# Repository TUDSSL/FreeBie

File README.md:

# Battery-free Bluetooth That Works

## Abstract
We present an architecture for intermittently-powered wireless communication systems that does not require any changes to the official protocol specification. Our core idea is to save the intermediate state of the wireless protocol to non-volatile memory within each connection interval. The protocol state is then deterministically restored at a predefined (harvested energy-dependent) time, which follows the connection interval. As a case study for our architecture, we introduce FreeBie: a battery-free intermittently-powered Bluetooth Low Energy (BLE) mote. To the best of our knowledge FreeBie is the first battery-free active wireless system that sustains bi-directional communication on intermittent harvested energy. The strength of our architecture is articulated by FreeBie consuming at least 9.5 times less power during device inactivity periods than a state-of-the-art BLE device.

<!--  -->
<!--  -->

## Artifact
We describe the process to reproduce the results presented in the paper.

### Repository structure
The diagram below describes structure and purpose of the most important directories of the FreeBie project.
* * *
 * Hardware
   * design: KiCad design files
   * schematic: PDF schematic
   * manufacturing: Bill of materials, Gerber files (per version)
 * Software
   * bin: Location of compiled application binaries
   * build: Location of build files
   * ckpt-app: Application process files per application
     * fw-update
     * smartwatch
     * template
   * ckpt-os: OS process files
   * config: CMake and project configuration files
   * libs: Drivers for external system components
   * platforms: Pin definitions
   * third-party
     * Cordio: Network process files
 * Evaluation
   * hosts
     * fw-update: Firmware for the firmware update host
     * smartwatch: Android app for smartwatch host
     * end-device
       * softdevice: Power comparison application
   * Plotting
     * plot.sh: Script generating all the plots in the paper
     * *.py: Figure-specific Python script invoked by plot.sh
 * Measurements
     * raw: Raw measurements
     * converted: Measurements converted to CSV format
     * traces: 24H trace and replay script
* * *

### Evaluation Setup
#### Code Generation and Programming Tools.

To compile FreeBie runtime we used the [GNU Arm Embedded Toolchain (9.3.1)](https://developer.arm.com/tools-and-software/open-source-software/developer-tools/gnu-toolchain/gnu-rm/downloads) and [CMake (3.19.1)](https://cmake.org) to build the project. To program the MCU we used the [J-Link debug probe](https://www.segger.com/products/debug-probes/j-link/models/j-link-edu) with the accompanying J-Link software. We used Linux in order compile and evaluate FreeBie. In this artifact, only Linux instructions are provided, although (untested) Windows or Mac OS could also be used to build the system.

#### Trace Recording Tools.

We used [Saleae Logic Pro 16 logic analyzer](http://downloads.saleae.com/specs/Logic+Pro+16+Product+Fact+Sheet.pdf), to record on-device FreeBie signals. To capture and analyze over-the-air master/end-device BLE packets exchanges we used [Nordic Semiconductors nRF sniffer](https://www.nordicsemi.com/Products/Development-tools/nRF-Sniffer-for-Bluetooth-LE) and [Wireshark](https://www.wireshark.org}) as protocol analyzer.

#### Controlled Test Environment.

We put FreeBie at the bottom of a closed light box. A wirelessly-controlled [LED bulb](https://www.philips-hue.com/en-gb/p/hue-white-ambiance-1-pack-e27/8718699673147) was installed at the top of the box to create repeatable and controlled light source. A [luminosity meter](https://www.uni-trend.com/html/product/Environmental/Environmental_Tester/Mini/UT383.html) was placed next to FreeBie mote to measure the exact luminosity projecting onto FreeBie's solar panels.

#### Power Measurement Process.

Connection event as well as the sleep power consumption for the [Packetcraft BLE network stack](https://github.com/packetcraft-inc/stacks), Nordic Semiconductors BLE SoftDevice and our intermittently-powered BLE stack were measured using a [STMicroelectronics X-NUCLEO-LPM01A power measurement board](https://www.st.com/en/evaluation-tools/x-nucleo-lpm01a.html). FreeBie's power consumption whilst the processor domain is off was measured with [Keithley 2450 SMU](https://download.tek.com/datasheet/1KW-60904-2_2450_Datasheet_072021.pdf). Power consumption during sleep and power off was measured at 1.8V. Power consumption of Packetcraft and SoftDevice is measured on the NRF52840 development kit, FreeBie power measurements are measured on the FreeBie mote. The BLE connection event power consumption for Packetcraft and SoftDevice was measured at a 1.8V, while BLE connection event for FreeBie was measured at 2.67V. We measure the connection event after the device has been running for five minutes, selecting a connection event with an empty PDU. The consumed energy results presented in Figure 12 Consumed Energy are computed as the sum of the energy consumed during the selected connection event and during the idle period (power off for FreeBie and sleep for Packetcraft and SoftDevice.).

#### FreeBie Hardware.

In order to reproduce the results of the paper a FreeBie mote is required. In the *Hardware* folder of the repository, all files to reproduce the mote are provided, such as the design files, Gerber files and the bill of materials.

### Building the FreeBie Software

In order to build the FreeBie software, from the *Software/build* directory the following commands need to be executed.

```bash
$ cmake ..
$ make install
```

As a result of these operations, the project is compiled and the resulting programmable binaries of the applications are moved to the *Software/bin* directory. Next, the compiled binary of the application that is being tested should be flashed to the FreeBie mote.

#### Programming the FreeBie Mote.

In order to assist with programming the FreeBie mote during intermittent operation, a button is placed next to the programming header on the mote. When this button is pressed during startup of the MCU, the MCU remains in a perpetual loop, allowing the device to be programmed. Note that this button only works during the start up of the MCU and during operation the mote might be unable to be flashed as the power to the MCU may be switched off.

## Results Reproduction

### Smartwatch Application

In order to reproduce the results related to the smartwatch application please make sure that the smartwatch binary is programmed to the FreeBie mote first.

#### Building the Android Application.

In order to build the Android application, open the project (located in *evaluation/hosts/smartwatch*) in the Android Studio and then proceed with building the APK. Then a *.apk* file should be available in the *evaluation/hosts/smartwatch/build/outputs/apk* directory of the project. The APK must then be installed on the phone through Android Studio or transferred to the phone and installed manually. When opening the app for the first time, it will ask for permissions that must be granted in order for the app to be able to function. For more information please refer to the [Android Developer website]().

#### Measurement.

First the logic analyzer is connected to the testpoints on the FreeBie mote. These testpoints provide the tracing information about the system state used to generate Figure 11 FreeBie smartwatch operation. For the measurement, the programmed FreeBie mote with the smartwatch binary is placed in the light box. The phone should be placed within range of the FreeBie mote for the devices to be able to connect. Next the variable light should be set to output the amount of light specified in the desired scenario to be replicated.

When the light is switched on the FreeBie mote starts harvesting energy and when enough energy is harvested the FreeBie mote should automatically switch on. The smartphone should then automatically connect to the FreeBie mote and time should appear on the LCD screen.

#### 24 hour experiment.

For the 24 hour experiment the same procedure as before is used, but instead of a static lighting, a script (available in the *Measurements/traces* directory) is used to replay a prerecorded luminosity trace of a person wearing a smartwatch for 24 hours. In order to execute the Python script, first the dependencies have to be installed, assuming Python is already installed. For this the following command needs to be executed.

```bash
$ cd Measurements/traces
$ pip install -r requirements.txt
```

Second the tool communicating with the light has to be installed and configured. Please follow the instructions on the website of the [tool](https://github.com/bahamas10/hue-cli). After the software is able to control the light, the script can be executed, replaying 24H of the prerecorded light trace.

```bash
$ python replay_lux.py -f \
  logger-2021-11-20_09-36-46-549.csv -skips 5
```

### Firmware Update Application

We first note that in order to reproduce the results presented in the smartwatch application please make sure the *fw-update* binary is programmed to the FreeBie mote.

#### Building and Flashing the Host Firmware.

First plug in the development kit and make sure that is is powered and detected. Then from the main project directory execute the following command.

```bash
$ cd Evaluation/hosts/          \
     fw-update/  \
     nRF5_SDK_17.0.2/           \
     examples/ble_central/      \
     ble_app_custom_c/          \
     pca10056/s140/armgcc
$ make
$ make flash_softdevice
$ make flash
```

The development kit should now be flashed with the correct firmware. Turn the development kit off and on. Now it is ready to start the firmware update as soon as the FreeBie mote is detected.

#### Measurement.

In order to generate the Evaluation of firmware update plot in FreeBie Evaluation section, the logic analyzer is connected to the test points on the FreeBie mote. These test points provide the tracing information about the system state used to generate Figure 13 Evaluation of firmware update. For the measurement, the programmed FreeBie mote with the *fw-update* binary is placed in the light box. The development kit, acting as firmware update host, should be placed within range of the FreeBie mote for the devices to be able to connect. For the firmware update application we did not connect the display to the FreeBie mote.

When the light is switched on the FreeBie mote starts harvesting energy and when enough energy is harvested the FreeBie mote should automatically switch on. The firmware update host should connect to the FreeBie mote and the firmware update should start automatically.

### Reference Comparison

In order to produce figures 8, 9 and 12 we used a minimal working example (named *template*) of our software that only actively uses the network process and the OS process. In this application after the BLE connection is established and the database discovery has been completed, only empty packets are sent. Hence, this forms a point of reference for other experiments.

#### Template Configuration.

From within the *CMakefile* file of *template*, checkpointing can be switched off by commenting the following lines:
```CMake
set(CHECKPOINTING 1)
set(CHECKPOINTING_TIMING 1)
```
Without checkpointing enabled this example serves as the Packetcraft comparison point and is representative of traditional operation; with checkpointing enabled---as FreeBie. When the checkpointing is active, a connection update request to the selected parameters is sent after connecting. To force the same behavior for the non-checkpointing version, the line *set(COMPARE_NO_CHECKPOINT 1)* needs to be uncommented. When modifying the CMakefiles, the code has to be recompiled with the same steps as described in Section Building the FreeBie Software.

#### Intermittent versus Non-intermittent.

In order to reproduce the results in Figure 8 the FreeBie mote is again placed in a light box at the specified light level and the information about the system state are recorded by the logic analyzer. The experiment is ran for both checkpointing enabled and checkpointing disabled. The non-checkpointed version runs out of energy and not be able to recover the connection as the system state is lost.

#### Connection Recovery.

For the results in Figure 9, the FreeBie mote is not powered by the solar panels but through an external power supply connected to the test point *VSol* on the back of the FreeBie mote. In this case *template* with connection recovery enabled (*set(RECOVER_CONNECTIONS 1)*) and checkpointing enabled is used. After a connection to the FreeBie mote has been established, the power to the device is disabled until the device suffers from a power failure. Then power is resumed and the device attempts recovery.

#### Power Measurement.

For the results in Figure 12 *template* is used with checkpointing disabled, serving as the Packetcraft comparison point; with checkpointing enabled---as FreeBie. As the comparison point of SoftDevice the code provided in *Evaluation/end-device/softdevice* is used. From the main project directory the code can be compiled and flashed using the following commands.

```bash
$ cd Evaluation/end-device/softdevice/ \
     examples/ble_peripheral/ \
     ble_app_pwr_profiling/ \
     pca10056/s140/armgcc
$ make
$ make flash_softdevice
$ make flash
```

Please refer to the Evaluation Setup Section for more information about the power measurement process.

### Plotting

By executing the *plot.sh* script in the *Plotting* directory all of the plots can be generated. Please note that due to the size of the 24 hour plot this might take more than 15 minutes and requires a system with at least 16GB of RAM. All plotting scripts use Python and assume Python is installed on the system; all Python dependencies can be installed via the *requirements.txt* file using the following commands.

Since the measurements files are large they are only included in the version of the artifact hosted on [Zenodo](https://doi.org/10.5281/zenodo.6583725)

```bash
$ cd Plotting
$ pip install -r requirements.txt
$ plot.sh
```

## License
The Project adopts the MIT license unless noted otherwise, As Packetcraft licenses its software stack under the Apache 2.0 license our code in the folder Software also adopts this license unless noted otherwise.

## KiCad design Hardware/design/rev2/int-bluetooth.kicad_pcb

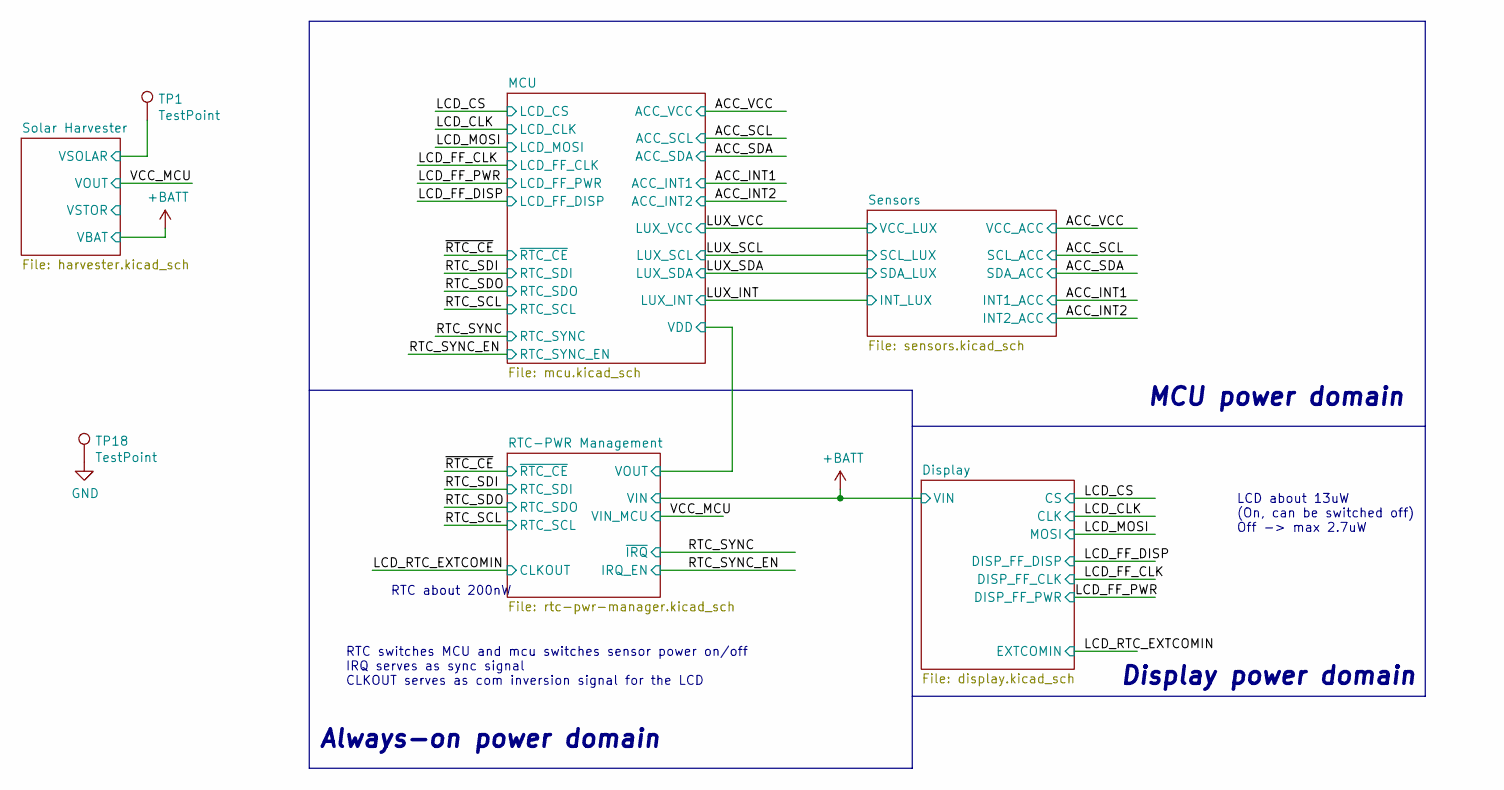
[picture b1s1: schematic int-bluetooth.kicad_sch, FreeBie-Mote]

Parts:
TP1, TP18: TestPoint; SMOX_PCB_TESTPOINT; MPN SMOX/060/B1/HT

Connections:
/Solar Harvester/VSOLAR: TP1.1; also elsewhere on the board
GND: TP18.1; also elsewhere on the board

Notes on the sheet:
Display power domain
LCD about 13uW (On, can be switched off) Off -> max 2.7uW
RTC about 200nW
Always-on power domain
RTC switches MCU and mcu switches sensor power on/off IRQ serves as sync signal CLKOUT serves as com inversion signal for the LCD
MCU power domain

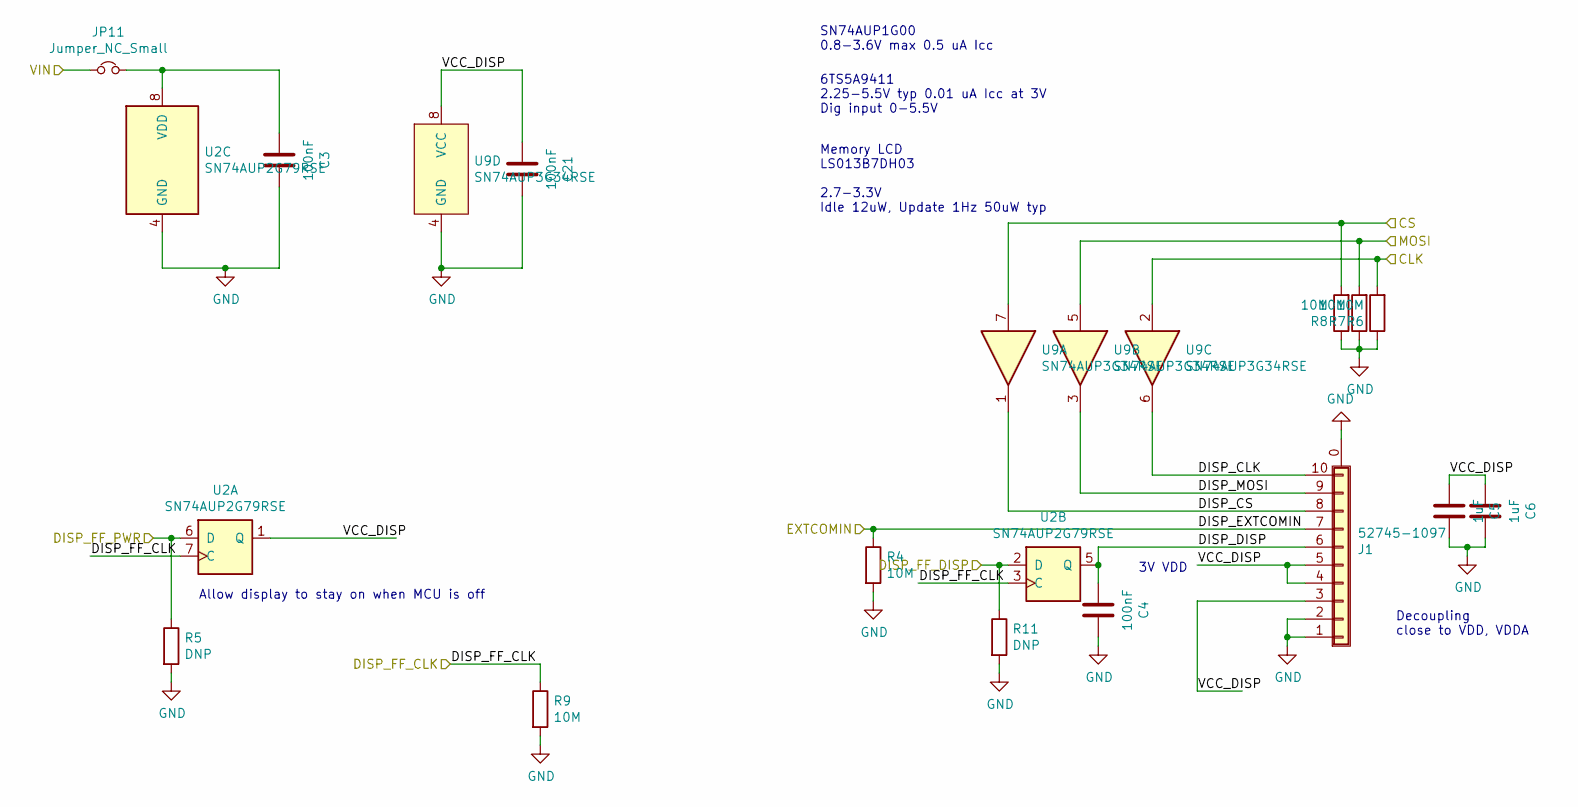
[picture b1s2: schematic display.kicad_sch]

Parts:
C3, C4, C21: 100nF; C_0402_1005Metric; MPN GRM155R71C104KA88J
C5, C6: 1uF; C_0402_1005Metric; MPN 0402ZD105KAT2A
J1: 52745-1097; FPC_10_TOP; MPN 52745-1097
JP11: Jumper_NC_Small; SolderJumper-small-nc
R4, R6, R7, R8, R9: 10M; R_0402_1005Metric; MPN RC0402FR-0710ML
R5, R11: DNP; R_0402_1005Metric
U2: SN74AUP2G79RSE; Texas_RSE_8_UQFN; MPN SN74AUP2G79RSE
U9: SN74AUP3G34RSE; Texas_RSE_8_UQFN; MPN SN74AUP3G34RSE

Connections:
+BATT: JP11.1; also elsewhere on the board
/Display/DISP_CLK: J1.10, U9.6
/Display/DISP_CS: J1.8, U9.1
/Display/DISP_DISP: C4.1, J1.6, U2.5 (Q)
/Display/DISP_MOSI: J1.9, U9.3
/Display/VCC_DISP: C5.1, C6.1, C21.1, J1.3, J1.4, J1.5, U2.1 (Q), U9.8 (VCC)
/LCD_CLK: R6.2, U9.2; also elsewhere on the board
/LCD_CS: R8.2, U9.7; also elsewhere on the board
/LCD_FF_CLK: R9.1, U2.3 (C), U2.7 (C); also elsewhere on the board
/LCD_FF_DISP: R11.1, U2.2 (D); also elsewhere on the board
/LCD_FF_PWR: R5.1, U2.6 (D); also elsewhere on the board
/LCD_MOSI: R7.2, U9.5; also elsewhere on the board
/LCD_RTC_EXTCOMIN: J1.7, R4.1; also elsewhere on the board
GND: C3.2, C4.2, C5.2, C6.2, C21.2, J1.0 (Shield), J1.1, J1.2, R4.2, R5.2, R6.1, R7.1, R8.1, R9.2, R11.2, U2.4 (GND), U9.4 (GND); also elsewhere on the board
unnamed: C3.1, JP11.2, U2.8 (VDD)

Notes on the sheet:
Memory LCD LS013B7DH03 2.7-3.3V Idle 12uW, Update 1Hz 50uW typ
SN74AUP1G00 0.8-3.6V max 0.5 uA Icc
Allow display to stay on when MCU is off
Decoupling close to VDD, VDDA
3V VDD
6TS5A9411 2.25-5.5V typ 0.01 uA Icc at 3V Dig input 0-5.5V

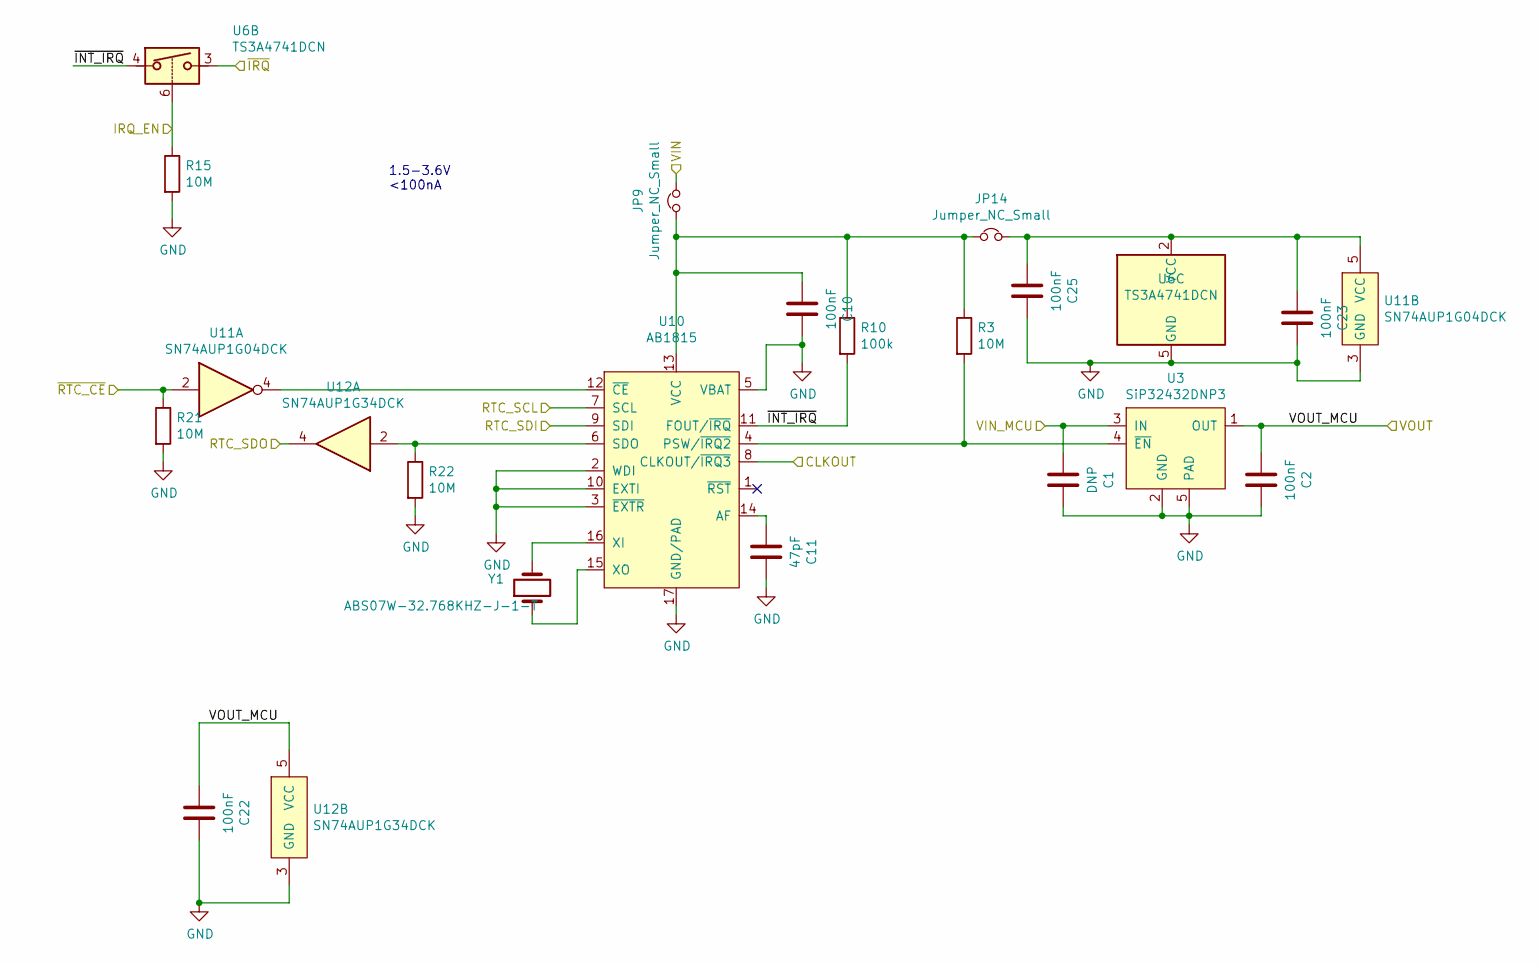
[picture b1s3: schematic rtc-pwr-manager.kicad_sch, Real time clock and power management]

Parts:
C1: DNP; C_0402_1005Metric
C2, C10, C22, C23, C25: 100nF; C_0402_1005Metric; MPN GRM155R71C104KA88J
C11: 47pF; C_0402_1005Metric; MPN GJM1555C1H470FB01D
JP9, JP14: Jumper_NC_Small; SolderJumper-small-nc
R3, R15, R21, R22: 10M; R_0402_1005Metric; MPN RC0402FR-0710ML
R10: 100k; R_0402_1005Metric; MPN RC0402FR-07100KL
U3: SiP32432DNP3; DFN-4-1EP_1.6x1.2mm_P0.5mm_EP; MPN SIP32432DNP3-T1GE4
U6: TS3A4741DCN; SOT-23-8; MPN TS3A4741DCN
U10: AB1815; QFN-16-1EP_3x3mm_P0.5mm_EP1.75x1.75mm_ThermalVias; MPN AM1815
U11: SN74AUP1G04DCK; Texas_R-PDSO-G5; MPN SN74AUP1G04DCK
U12: SN74AUP1G34DCK; Texas_R-PDSO-G5; MPN SN74AUP1G34DCK
Y1: ABS07W-32.768KHZ-J-1-T; Crystal_SMD_3215-2Pin_3.2x1.5mm; MPN ABS07W-32.768KHZ-J-1-T

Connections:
+BATT: JP9.2; also elsewhere on the board
/LCD_RTC_EXTCOMIN: U10.8 (CLKOUT/~IRQ3); also elsewhere on the board
/RTC-PWR Management/VOUT_MCU: C2.1, C22.1, U3.1 (OUT), U12.5 (VCC); also elsewhere on the board
/RTC-PWR Management/~INT_IRQ: R10.2, U6.4, U10.11 (FOUT/~IRQ)
/RTC_SCL: U10.7 (SCL); also elsewhere on the board
/RTC_SDI: U10.9 (SDI); also elsewhere on the board
/RTC_SDO: U12.4; also elsewhere on the board
/RTC_SYNC: U6.3; also elsewhere on the board
/RTC_SYNC_EN: R15.1, U6.6; also elsewhere on the board
/VCC_MCU: C1.1, U3.3 (IN); also elsewhere on the board
/~RTC_CE: R21.1, U11.2; also elsewhere on the board
GND: C1.2, C2.2, C10.2, C11.2, C22.2, C23.2, C25.2, R15.2, R21.2, R22.2, U3.2 (GND), U3.5 (PAD), U6.5 (GND), U10.2 (WDI), U10.3 (~EXTR), U10.5 (VBAT), U10.10 (EXTI), U10.17 (GND/PAD), U11.3 (GND), U12.3 (GND); also elsewhere on the board
unnamed: C10.1, JP9.1, JP14.1, R3.1, R10.1, U10.13 (VCC)
unnamed: C11.1, U10.14 (AF)
unnamed: C23.1, C25.1, JP14.2, U6.2 (VCC), U11.5 (VCC)
unnamed: R3.2, U3.4 (~EN), U10.4 (PSW/~IRQ2)
unnamed: R22.1, U10.6 (SDO), U12.2
unnamed: U10.12 (~CE), U11.4
unnamed: U10.15 (XO), Y1.1
unnamed: U10.16 (XI), Y1.2

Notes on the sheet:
1.5-3.6V <100nA

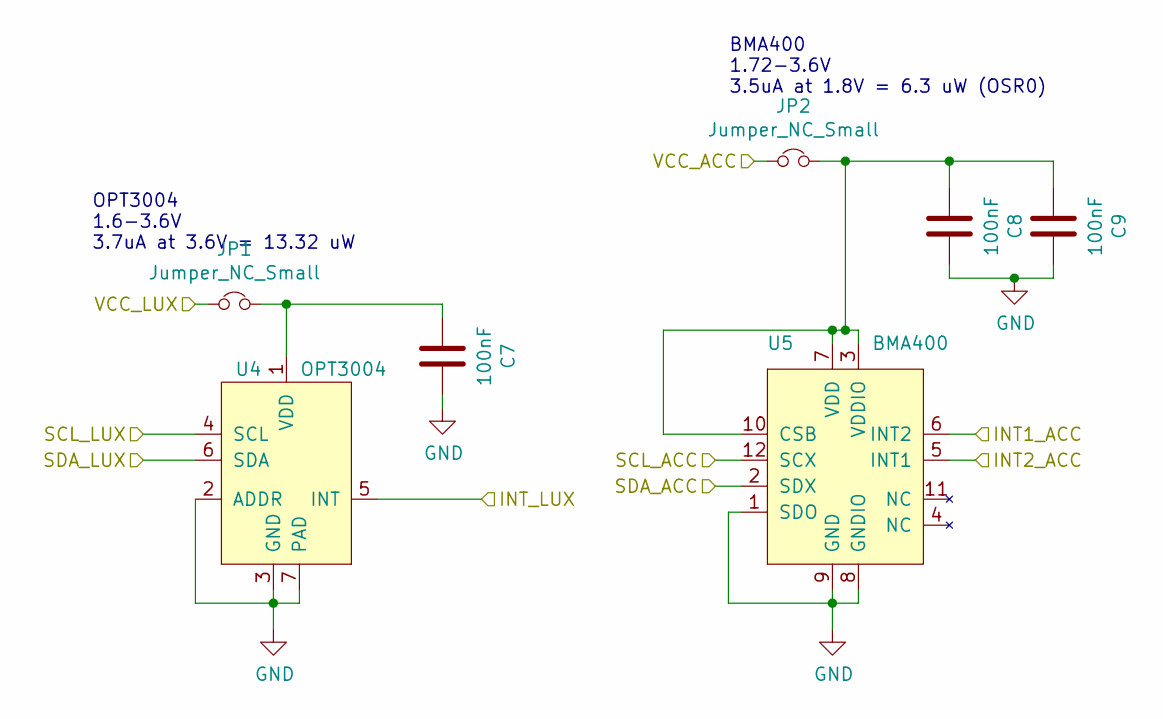
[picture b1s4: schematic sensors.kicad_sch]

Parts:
C7, C8, C9: 100nF; C_0402_1005Metric; MPN GRM155R71C104KA88J
JP1, JP2: Jumper_NC_Small; SolderJumper-small-nc
U4: OPT3004; USON6-OPT3004; MPN OPT3004DNPR
U5: BMA400; MPN BMA400

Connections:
/ACC_INT1: U5.6 (INT2); also elsewhere on the board
/ACC_INT2: U5.5 (INT1); also elsewhere on the board
/ACC_SCL: U5.12 (SCX); also elsewhere on the board
/ACC_SDA: U5.2 (SDX); also elsewhere on the board
/ACC_VCC: JP2.1; also elsewhere on the board
/LUX_INT: U4.5 (INT); also elsewhere on the board
/LUX_SCL: U4.4 (SCL); also elsewhere on the board
/LUX_SDA: U4.6 (SDA); also elsewhere on the board
/LUX_VCC: JP1.1; also elsewhere on the board
GND: C7.2, C8.2, C9.2, U4.2 (ADDR), U4.3 (GND), U4.7 (PAD), U5.1 (SDO), U5.8 (GNDIO), U5.9 (GND); also elsewhere on the board
unnamed: C7.1, JP1.2, U4.1 (VDD)
unnamed: C8.1, C9.1, JP2.2, U5.3 (VDDIO), U5.7 (VDD), U5.10 (CSB)

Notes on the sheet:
OPT3004 1.6-3.6V 3.7uA at 3.6V = 13.32 uW
BMA400 1.72-3.6V 3.5uA at 1.8V = 6.3 uW (OSR0)

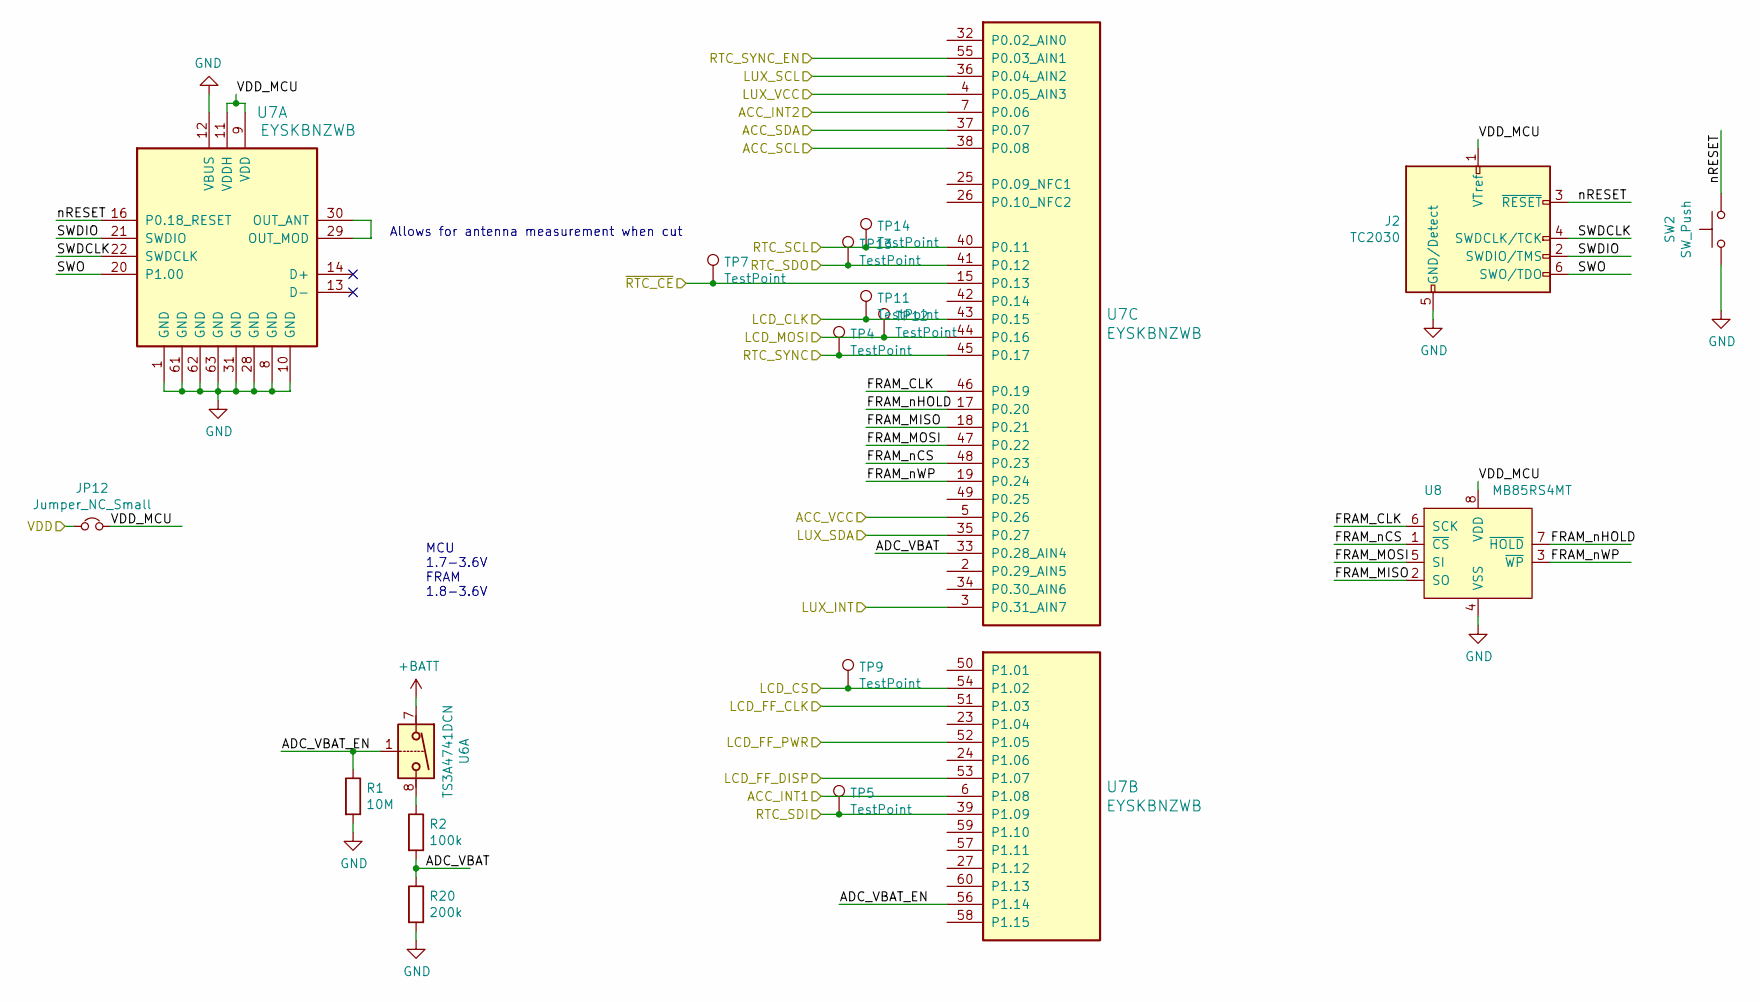
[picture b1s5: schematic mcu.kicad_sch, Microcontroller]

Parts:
J2: TC2030; Tag-Connect_TC2030-IDC-NL_2x03_P1.27mm_Vertical
JP12: Jumper_NC_Small; SolderJumper-small-nc
R1: 10M; R_0402_1005Metric; MPN RC0402FR-0710ML
R2: 100k; R_0402_1005Metric; MPN RC0402FR-07100KL
R20: 200k; R_0402_1005Metric; MPN RC0402FR-07200KL
SW2: SW_Push; SW_SPST_B3U-1000P; MPN B3U-1000P
TP4, TP5, TP7, TP9, TP11, TP12, TP13, TP14: TestPoint; SMOX_PCB_TESTPOINT; MPN SMOX/060/B1/HT
U6: TS3A4741DCN; SOT-23-8; MPN TS3A4741DCN
U7: EYSKBNZWB; MPN EYSKBNZWB
U8: MB85RS4MT; SO-8_5.3x6.2mm_P1.27mm; MPN MB85RS4MT

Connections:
+BATT: U6.7; also elsewhere on the board
/ACC_INT1: U7.6 (P1.08); also elsewhere on the board
/ACC_INT2: U7.7 (P0.06); also elsewhere on the board
/ACC_SCL: U7.38 (P0.08); also elsewhere on the board
/ACC_SDA: U7.37 (P0.07); also elsewhere on the board
/ACC_VCC: U7.5 (P0.26); also elsewhere on the board
/LCD_CLK: TP11.1, U7.43 (P0.15); also elsewhere on the board
/LCD_CS: TP9.1, U7.54 (P1.02); also elsewhere on the board
/LCD_FF_CLK: U7.51 (P1.03); also elsewhere on the board
/LCD_FF_DISP: U7.53 (P1.07); also elsewhere on the board
/LCD_FF_PWR: U7.52 (P1.05); also elsewhere on the board
/LCD_MOSI: TP12.1, U7.44 (P0.16); also elsewhere on the board
/LUX_INT: U7.3 (P0.31_AIN7); also elsewhere on the board
/LUX_SCL: U7.36 (P0.04_AIN2); also elsewhere on the board
/LUX_SDA: U7.35 (P0.27); also elsewhere on the board
/LUX_VCC: U7.4 (P0.05_AIN3); also elsewhere on the board
/MCU/ADC_VBAT: R2.2, R20.1, U7.33 (P0.28_AIN4)
/MCU/ADC_VBAT_EN: R1.1, U6.1, U7.56 (P1.14)
/MCU/FRAM_CLK: U7.46 (P0.19), U8.6 (SCK)
/MCU/FRAM_MISO: U7.18 (P0.21), U8.2 (SO)
/MCU/FRAM_MOSI: U7.47 (P0.22), U8.5 (SI)
/MCU/FRAM_nCS: U7.48 (P0.23), U8.1 (~CS)
/MCU/FRAM_nHOLD: U7.17 (P0.20), U8.7 (~HOLD)
/MCU/FRAM_nWP: U7.19 (P0.24), U8.3 (~WP)
/MCU/SWDCLK: J2.4 (SWDCLK/TCK), U7.22 (SWDCLK)
/MCU/SWDIO: J2.2 (SWDIO/TMS), U7.21 (SWDIO)
/MCU/SWO: J2.6 (SWO/TDO), U7.20 (P1.00)
/MCU/VDD_MCU: J2.1 (VTref), JP12.2, U7.9 (VDD), U7.11 (VDDH), U8.8 (VDD)
/MCU/nRESET: J2.3 (~RESET), SW2.2, U7.16 (P0.18_RESET)
/RTC-PWR Management/VOUT_MCU: JP12.1; also elsewhere on the board
/RTC_SCL: TP14.1, U7.40 (P0.11); also elsewhere on the board
/RTC_SDI: TP5.1, U7.39 (P1.09); also elsewhere on the board
/RTC_SDO: TP13.1, U7.41 (P0.12); also elsewhere on the board
/RTC_SYNC: TP4.1, U7.45 (P0.17); also elsewhere on the board
/RTC_SYNC_EN: U7.55 (P0.03_AIN1); also elsewhere on the board
/~RTC_CE: TP7.1, U7.15 (P0.13); also elsewhere on the board
GND: J2.5 (GND/Detect), R1.2, R20.2, SW2.1, U7.1 (GND), U7.8 (GND), U7.10 (GND), U7.12 (VBUS), U7.28 (GND), U7.31 (GND), U7.61 (GND), U7.62 (GND), U7.63 (GND), U8.4 (VSS); also elsewhere on the board
unnamed: R2.1, U6.8
unnamed: U7.29 (OUT_MOD), U7.30 (OUT_ANT)

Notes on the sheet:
MCU 1.7-3.6V FRAM 1.8-3.6V
Allows for antenna measurement when cut

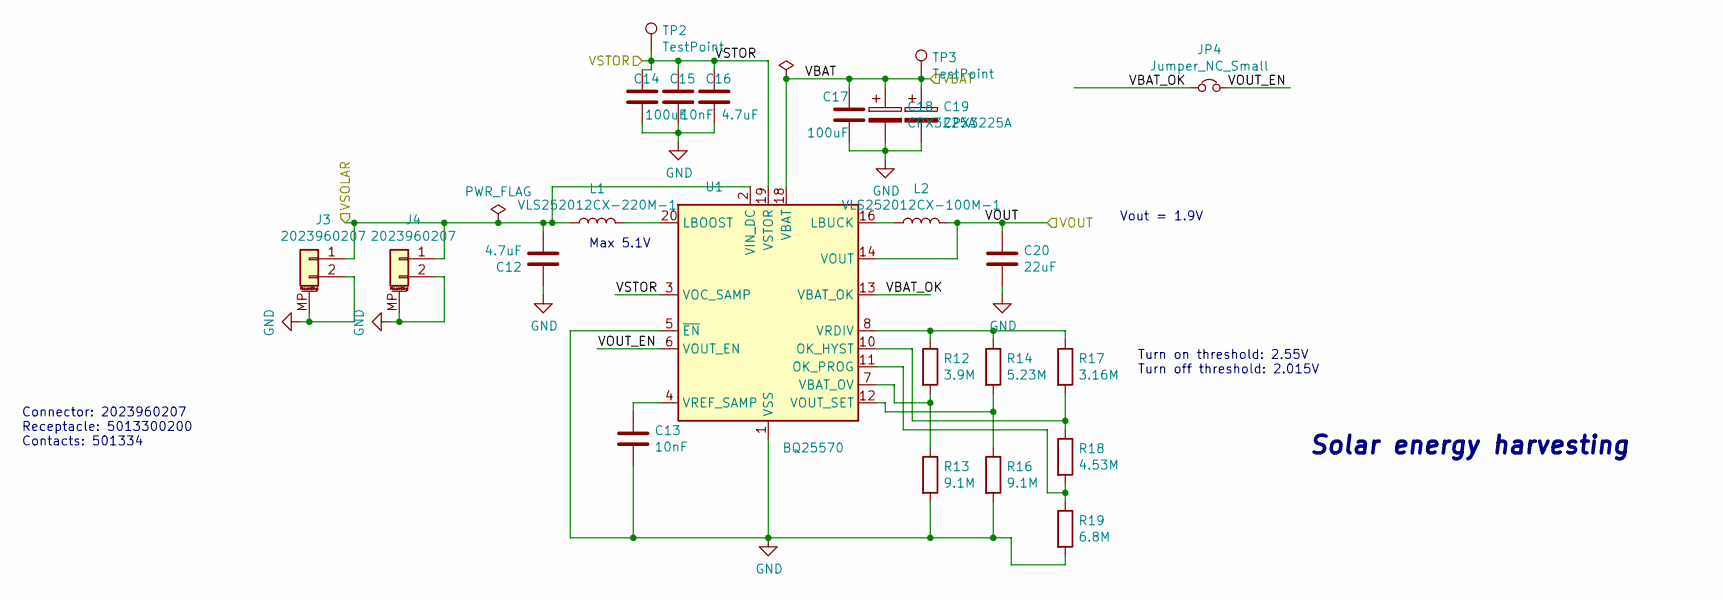
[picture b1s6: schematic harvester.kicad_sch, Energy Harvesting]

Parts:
C12, C16: 4.7uF; C_0402_1005Metric; MPN LMK105BBJ475MVLF
C13, C15: 10nF; C_0402_1005Metric; MPN GCM155R71H103KA55D
C14, C17: 100uF; C_1210_3225Metric
C18, C19: CPX3225A; MPN CPX3225A
C20: 22uF; C_0603_1608Metric; MPN GRM188R60J226MEA0D
J3, J4: 2023960207; Molex_Pico-Clasp_202396-0207_1x02-1MP_P1.00mm_Horizontal; MPN 202396-0207
JP4: Jumper_NC_Small; SolderJumper-small-nc
L1: VLS252012CX-220M-1; VLS252012CX-1; MPN VLS252012CX-220M-1
L2: VLS252012CX-100M-1; VLS252012CX-1; MPN VLS252012CX-100M-1
R12: 3.9M; R_0402_1005Metric; MPN MCHVR02FTFY3904
R13, R16: 9.1M; R_0402_1005Metric; MPN CRCW04029M10FKED
R14: 5.23M; R_0402_1005Metric; MPN CRCW04025M23FKED
R17: 3.16M; R_0402_1005Metric; MPN CRCW04023M16FKED
R18: 4.53M; R_0402_1005Metric; MPN RMCF0402FT4M53
R19: 6.8M; R_0402_1005Metric; MPN MCHVR02FTFY6804
TP2, TP3: TestPoint; SMOX_PCB_TESTPOINT; MPN SMOX/060/B1/HT
U1: BQ25570; QFN-20-1EP_3.5x3.5mm_P0.5mm_EP2x2mm; MPN BQ25570RGR

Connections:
+BATT: C17.2, C18.1, C19.1, TP3.1, U1.18 (VBAT); also elsewhere on the board
/Solar Harvester/VBAT_OK: JP4.1, U1.13 (VBAT_OK)
/Solar Harvester/VOUT_EN: JP4.2, U1.6 (VOUT_EN)
/Solar Harvester/VSOLAR: C12.2, J3.1, J4.1, L1.1, U1.2 (VIN_DC); also elsewhere on the board
/Solar Harvester/VSTOR: C14.2, C15.2, C16.2, TP2.1, U1.3 (VOC_SAMP), U1.19 (VSTOR)
/VCC_MCU: C20.1, L2.2, U1.14 (VOUT); also elsewhere on the board
GND: C12.1, C13.2, C14.1, C15.1, C16.1, C17.1, C18.2, C19.2, C20.2, J3.2, J3.MP (MountPin), J4.2, J4.MP (MountPin), R13.2, R16.2, R19.2, U1.1 (VSS), U1.5 (~EN), U1.9 (VSS), U1.15 (VSS), U1.17 (VSS), U1.21 (VSS); also elsewhere on the board
unnamed: C13.1, U1.4 (VREF_SAMP)
unnamed: L1.2, U1.20 (LBOOST)
unnamed: L2.1, U1.16 (LBUCK)
unnamed: R12.1, R14.1, R17.1, U1.8 (VRDIV)
unnamed: R12.2, R13.1, U1.7 (VBAT_OV)
unnamed: R14.2, R16.1, U1.12 (VOUT_SET)
unnamed: R17.2, R18.1, U1.10 (OK_HYST)
unnamed: R18.2, R19.1, U1.11 (OK_PROG)

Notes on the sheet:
Max 5.1V
Solar energy harvesting
Vout = 1.9V
Turn on threshold: 2.55V Turn off threshold: 2.015V
Connector: 2023960207 Receptacle: 5013300200 Contacts: 501334

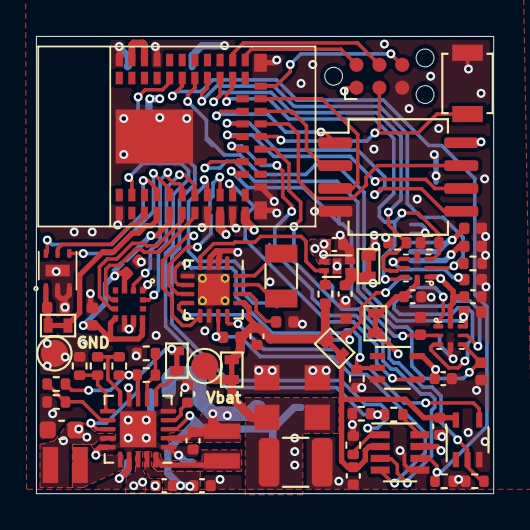
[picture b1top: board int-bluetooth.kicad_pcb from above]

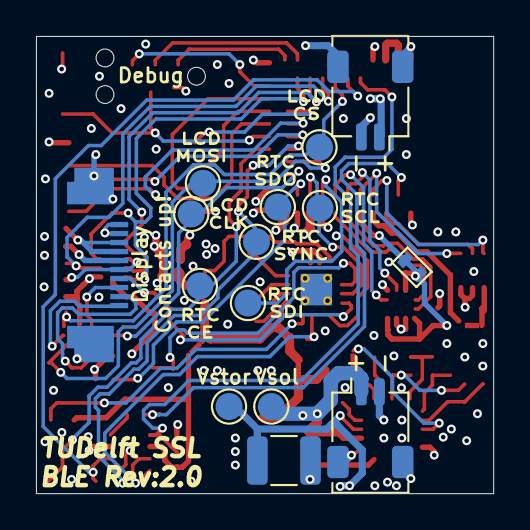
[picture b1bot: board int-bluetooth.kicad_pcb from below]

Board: 4 copper layers, 25.4 x 25.4 mm, 85 parts (15 on the bottom side), 70 nets.

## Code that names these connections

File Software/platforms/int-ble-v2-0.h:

/*************************************************************************************************/
/*!
 *  Copyright (c) 2022 Delft University of Technology.
 *  Jasper de Winkel, Haozhe Tang and Przemyslaw Pawelczak
 *
 *  Licensed under the Apache License, Version 2.0 (the "License");
 *  you may not use this file except in compliance with the License.
 *  You may obtain a copy of the License at
 *
 *      http://www.apache.org/licenses/LICENSE-2.0
 *
 *  Unless required by applicable law or agreed to in writing, software
 *  distributed under the License is distributed on an "AS IS" BASIS,
 *  WITHOUT WARRANTIES OR CONDITIONS OF ANY KIND, either express or implied.
 *  See the License for the specific language governing permissions and
 *  limitations under the License.
 */
/*************************************************************************************************/


#ifndef PLATFORMS_INT_BLE_V2_0_H_
#define PLATFORMS_INT_BLE_V2_0_H_

#include "nrf.h"

// LCD
#define LCD_CLK 15 // P0.15
#define LCD_MOSI 16 // P0.16
#define LCD_CS 34 // P1.02

#define LCD_FF_CLK 35 // P1.03
#define LCD_FF_PWR 37 // P1.05
#define LCD_FF_DISP 39 // P1.07

#ifndef LCD_PINS_OCCUPIED
#define DEBUG_INFO_NET_CKPT LCD_CLK
#define DEBUG_INFO_FW_CONTENT LCD_MOSI
#define DEBUG_INFO_APP_CKPT LCD_CS
#endif

// Lux
#define LUX_VCC 5 // P0.05A
#define LUX_SCL 4 // P0.04A
#define LUX_SDA 27 // P0.27

#define LUX_INT 31 // P0.31A

#define DEBUG_INFO_CKPT LUX_SCL
#define DEBUG_INFO_BLE LUX_SDA
#define DEBUG_INFO_APP LUX_INT

// Acc
#define ACC_VCC 26 // P0.26
#define ACC_SCL 8 // P0.08
#define ACC_SDA 7 // P0.07

#define ACC_INT1 40 // P1.08
#define ACC_INT2 6 // P0.06

// FRAM
#define FRAM_CS   23 // P0.23
#define FRAM_MOSI 22 // P0.22
#define FRAM_MISO 21 // P0.21
#define FRAM_CLK  19 // P0.19
#define FRAM_WP   24 // P0.24
#define FRAM_HOLD 20 // P0.20

// RTC
#define RTC_CS 13 // P0.13
#define RTC_SDO 12 // P0.12
#define RTC_SDI 41 // P1.09
#define RTC_SCL 11 // P0.11

#define RTC_SYNC_EN 3 // P0.03A
#define RTC_SYNC 17 // P0.17

#define ADC_VBAT 28 // P0.28A
#define ADC_VBAT_EN 46 // P1.14

#endif /* PLATFORMS_INT_BLE_V2_0_H_ */

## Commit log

2022-05-26 Added Zenodo link
